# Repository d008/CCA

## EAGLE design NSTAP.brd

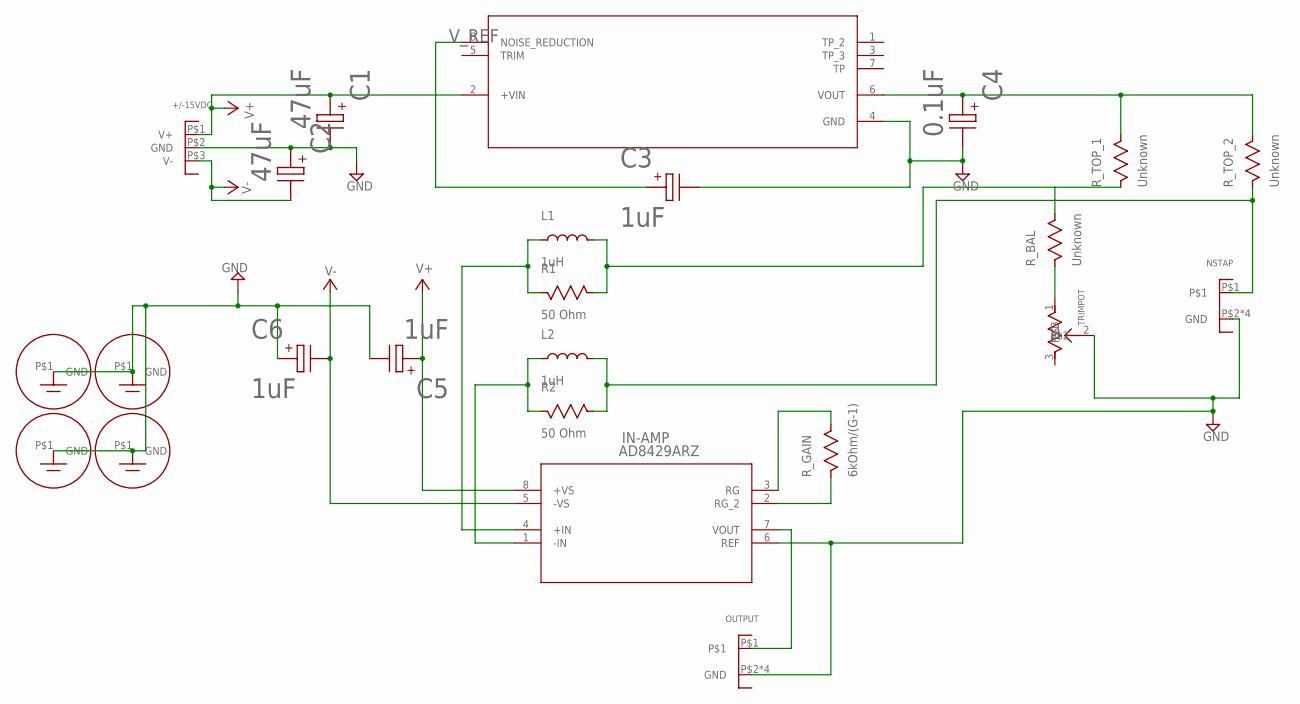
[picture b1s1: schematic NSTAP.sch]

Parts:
+/-15VDC: CONNECTOR_3COND""; SCREW_TERM3X-OST
C1, C2: 47uF; BRD_0075X050-P
C3, C5, C6: 1uF; BRD_0075X025-P
C4: 0.1uF; BRD_0075X050-P
IN-AMP: AD8429ARZ; R_8
L1, L2: 1uH; BRD_0075X150
NSTAP: CONNECTOR_COAXAMPHENOL-2037; BNC_AMPHENOL
OUTPUT: CONNECTOR_COAXAMPHENOL-2037; BNC_AMPHENOL
R1, R2: 50 Ohm; BRD_0075X100
R_BAL: Unknown; BRD_0075X100
R_GAIN: 6kOhm/(G-1); BRD_0075X100
R_TOP_1, R_TOP_2: Unknown; BRD_0075X100
TRIMPOT: TRIM_POT
U$1, U$2, U$3, U$4: GND-SCREW4MM; GND-SCREW_4MM
V_REF: AD587KNZ; N_8

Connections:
GND: +/-15VDC.P$2 (GND), C1.P$2, C2.P$1, C3.P$2, C4.P$2, C5.P$2, C6.P$1, IN-AMP.6 (REF), NSTAP.P$2 (GND), NSTAP.P$3 (GND), NSTAP.P$4 (GND), NSTAP.P$5 (GND), OUTPUT.P$2 (GND), OUTPUT.P$3 (GND), OUTPUT.P$4 (GND), OUTPUT.P$5 (GND), TRIMPOT.2, U$1.P$1, U$2.P$1, U$3.P$1, U$4.P$1, V_REF.4 (GND)
unnamed: C3.P$1, V_REF.8 (NOISE_REDUCTION)
unnamed: R_BAL.P$1, TRIMPOT.1
unnamed: IN-AMP.3 (RG), R_GAIN.P$2
unnamed: IN-AMP.2 (RG_2), R_GAIN.P$1
unnamed: IN-AMP.7 (VOUT), OUTPUT.P$1
unnamed: IN-AMP.4 (+IN), L1.P$1, R1.P$1
unnamed: IN-AMP.1 (-IN), L2.P$1, R2.P$1
unnamed: L2.P$2, NSTAP.P$1, R2.P$2, R_TOP_2.P$1
unnamed: C4.P$1, R_TOP_1.P$2, R_TOP_2.P$2, V_REF.6 (VOUT)
unnamed: L1.P$2, R1.P$2, R_BAL.P$2, R_TOP_1.P$1
V+: +/-15VDC.P$1 (V+), C1.P$1, C5.P$1, IN-AMP.8 (+VS), V_REF.2 (+VIN)
V-: +/-15VDC.P$3 (V-), C2.P$2, C6.P$2, IN-AMP.5 (-VS)

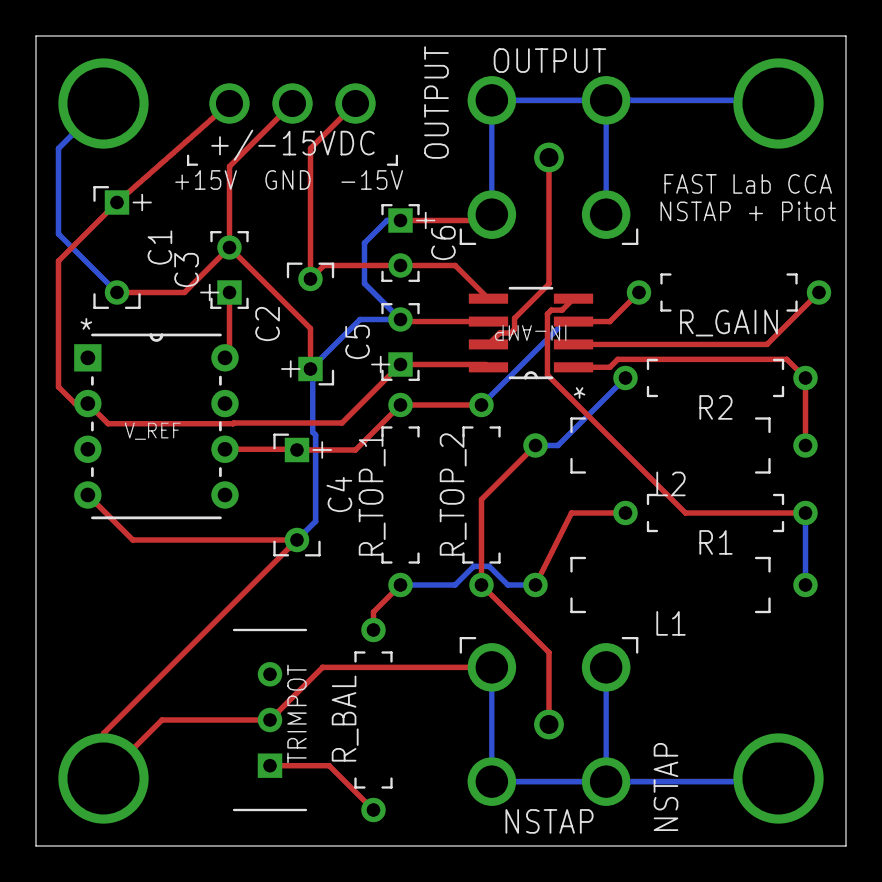
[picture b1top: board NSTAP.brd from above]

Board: 2 copper layers, 45.0 x 45.0 mm, 24 parts (0 on the bottom side), 13 nets.
